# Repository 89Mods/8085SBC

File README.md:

# 8085 SBC

This repo contains all the source files for my i8085 SBC. For more information, see the READMEs in the sub-directories, and the writeup [on my website](https://tholin.dev/8085).

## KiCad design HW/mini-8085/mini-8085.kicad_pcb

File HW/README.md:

# Hardware

Here are the KiCad projects for all the hardware for the SBC, including the ROM carts.

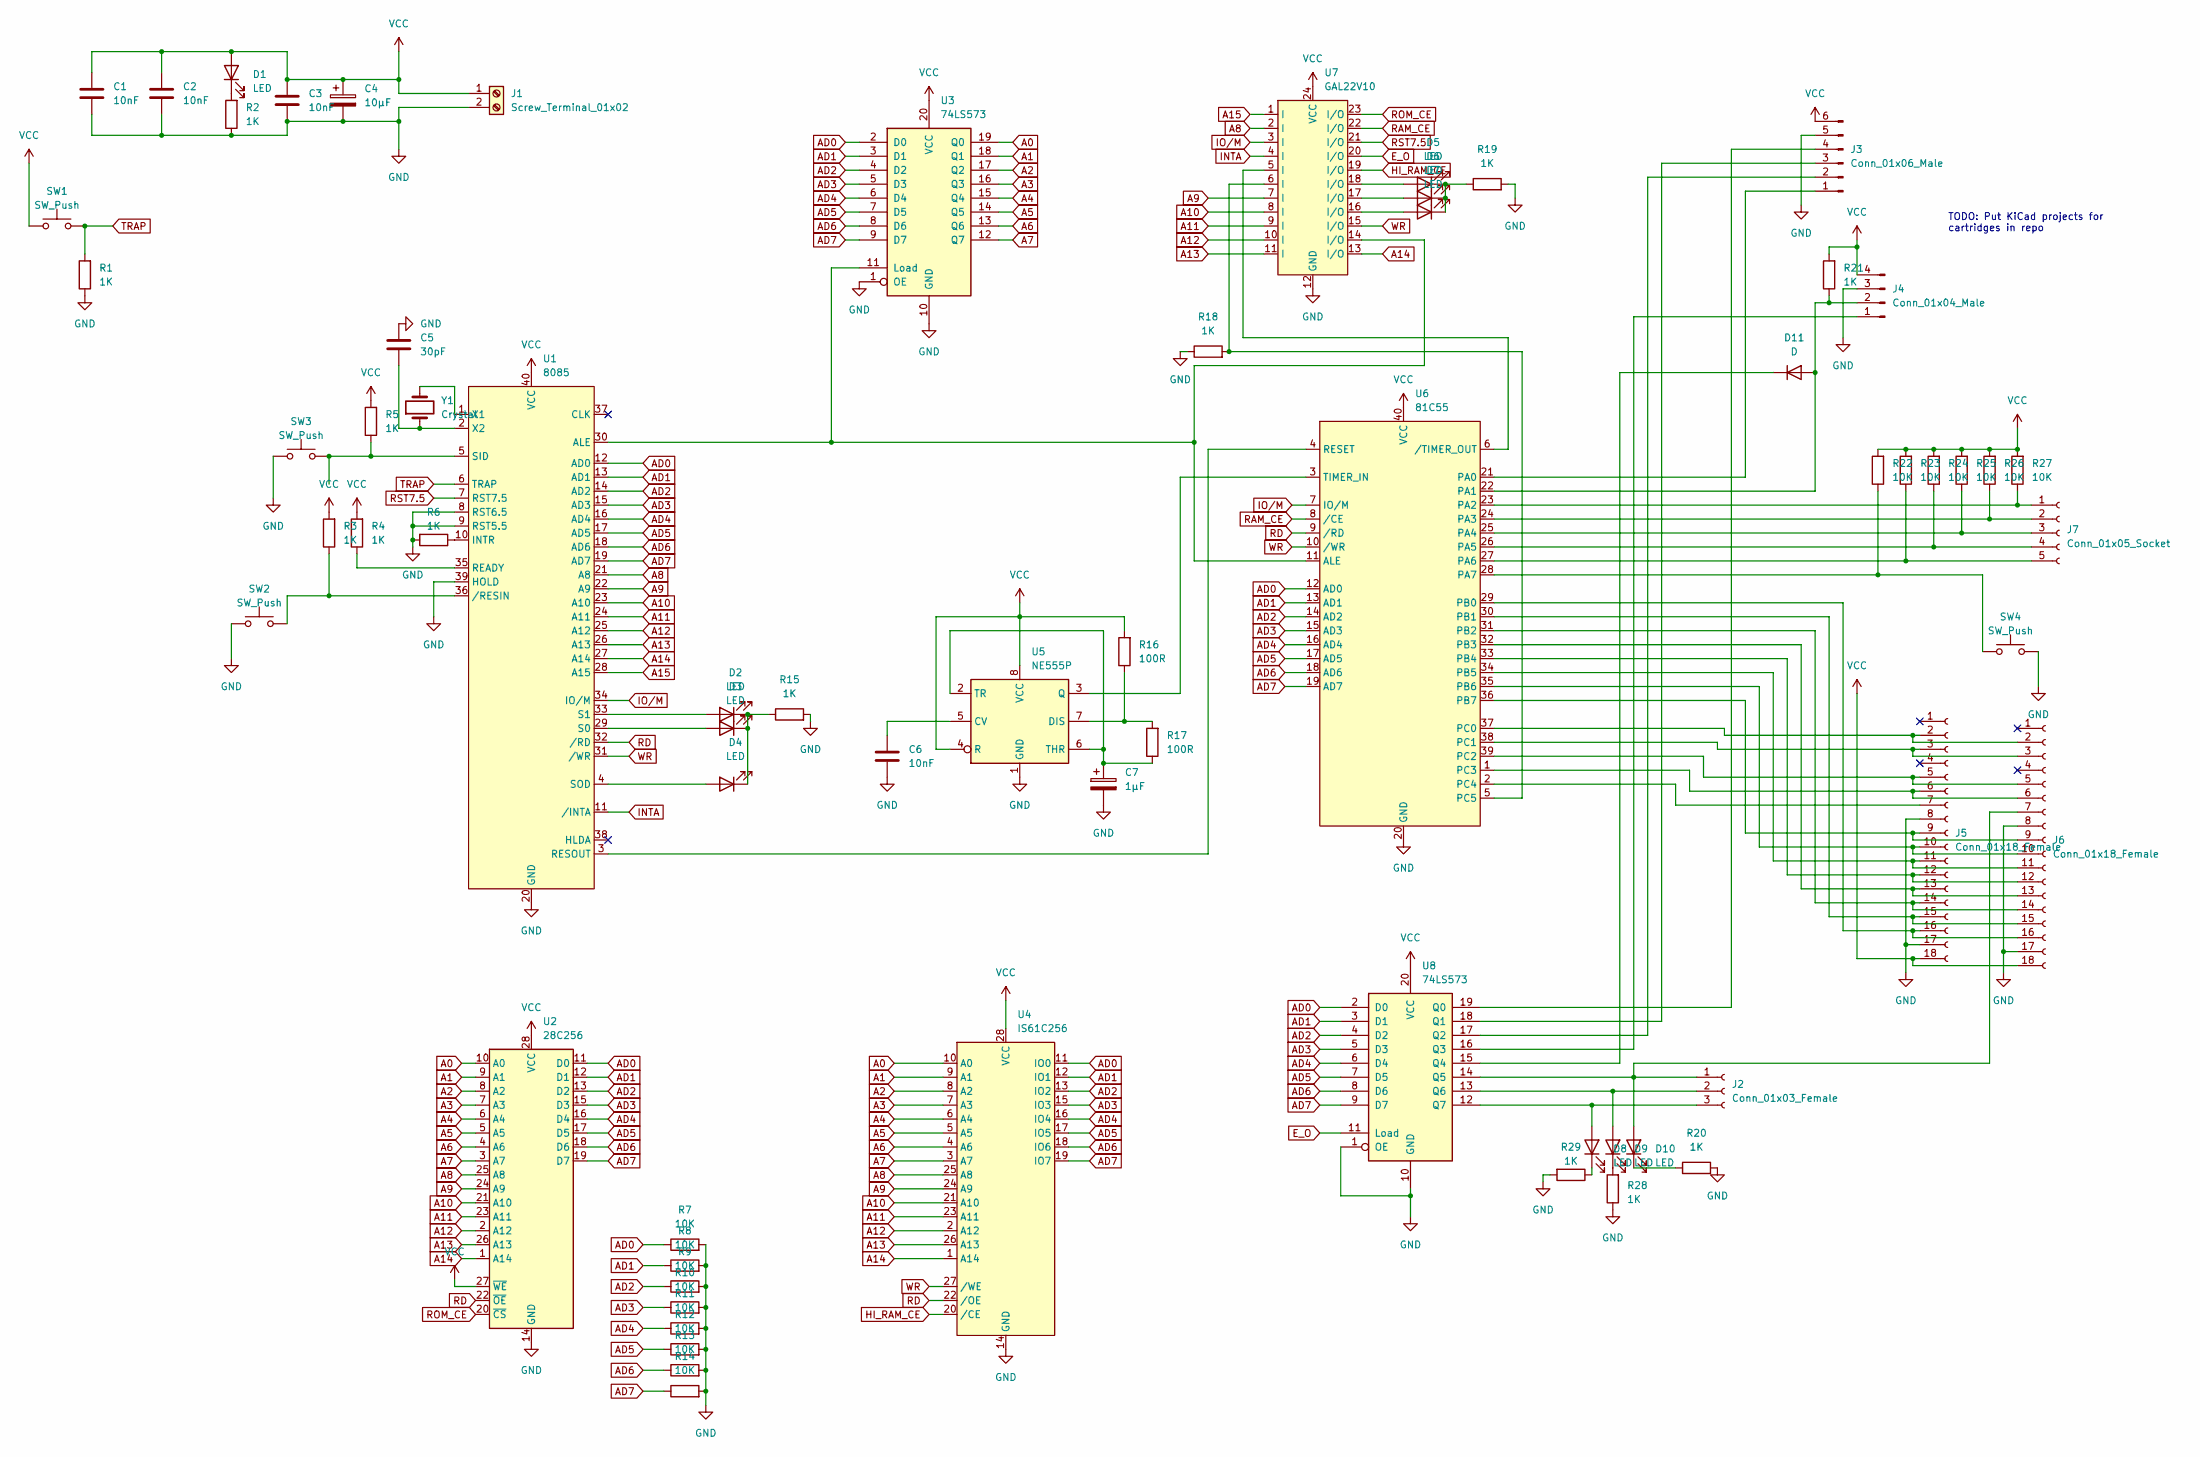
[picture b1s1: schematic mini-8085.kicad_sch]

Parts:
C1, C2, C3, C6: 10nF; C_Disc_D4.3mm_W1.9mm_P5.00mm
C4: 10µF; CP_Radial_D4.0mm_P1.50mm
C5: 30pF; C_Disc_D3.4mm_W2.1mm_P2.50mm
C7: 1µF; CP_Radial_D4.0mm_P1.50mm
D1, D2, D3, D4, D5, D6, D7, D8, D9, D10: LED; LED_D3.0mm
D11: D; D_A-405_P12.70mm_Horizontal
J1: Screw_Terminal_01x02; TerminalBlock_bornier-2_P5.08mm
J2: Conn_01x03_Female; PinHeader_1x03_P2.54mm_Vertical
J3: Conn_01x06_Male; PinHeader_1x06_P2.54mm_Vertical
J4: Conn_01x04_Male; PinHeader_1x04_P2.54mm_Vertical
J5, J6: Conn_01x18_Female; PinHeader_1x18_P2.54mm_Vertical
J7: Conn_01x05_Socket; PinHeader_1x05_P2.54mm_Vertical
R1, R2, R3, R4, R5, R6, R15, R18, R19, R20, R21, R28, R29: 1K; R_Axial_DIN0204_L3.6mm_D1.6mm_P7.62mm_Horizontal
R7, R8, R9, R10, R11, R12, R13, R14, R22, R23, R24, R25, R26, R27: 10K; R_Axial_DIN0204_L3.6mm_D1.6mm_P7.62mm_Horizontal
R16, R17: 100R; R_Axial_DIN0204_L3.6mm_D1.6mm_P7.62mm_Horizontal
SW1, SW2, SW3, SW4: SW_Push; SW_PUSH_6mm_H7.3mm
U1: 8085; DIP-40_W15.24mm
U2: 28C256; DIP-28_W15.24mm
U3, U8: 74LS573; DIP-20_W7.62mm
U4: IS61C256; DIP-28_W7.62mm
U5: NE555P; DIP-8_W7.62mm
U6: 81C55; DIP-40_W15.24mm
U7: GAL22V10; DIP-24_W7.62mm
Y1: Crystal; Resonator-2Pin_W7.0mm_H2.5mm

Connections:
A0: U2.10 (A0), U3.19 (Q0), U4.10 (A0)
A1: U2.9 (A1), U3.18 (Q1), U4.9 (A1)
A2: U2.8 (A2), U3.17 (Q2), U4.8 (A2)
A3: U2.7 (A3), U3.16 (Q3), U4.7 (A3)
A4: U2.6 (A4), U3.15 (Q4), U4.6 (A4)
A5: U2.5 (A5), U3.14 (Q5), U4.5 (A5)
A6: U2.4 (A6), U3.13 (Q6), U4.4 (A6)
A7: U2.3 (A7), U3.12 (Q7), U4.3 (A7)
A8: U1.21 (A8), U2.25 (A8), U4.25 (A8), U7.2 (I)
A9: U1.22 (A9), U2.24 (A9), U4.24 (A9), U7.7 (I)
A10: U1.23 (A10), U2.21 (A10), U4.21 (A10), U7.8 (I)
A11: U1.24 (A11), U2.23 (A11), U4.23 (A11), U7.9 (I)
A12: U1.25 (A12), U2.2 (A12), U4.2 (A12), U7.10 (I)
A13: U1.26 (A13), U2.26 (A13), U4.26 (A13), U7.11 (I)
A14: U1.27 (A14), U2.1 (A14), U4.1 (A14), U7.13 (I/O)
A15: U1.28 (A15), U7.1 (I)
AD0: R7.1, U1.12 (AD0), U2.11 (D0), U3.2 (D0), U4.11 (IO0), U6.12 (AD0), U8.2 (D0)
AD1: R8.1, U1.13 (AD1), U2.12 (D1), U3.3 (D1), U4.12 (IO1), U6.13 (AD1), U8.3 (D1)
AD2: R9.1, U1.14 (AD2), U2.13 (D2), U3.4 (D2), U4.13 (IO2), U6.14 (AD2), U8.4 (D2)
AD3: R10.1, U1.15 (AD3), U2.15 (D3), U3.5 (D3), U4.15 (IO3), U6.15 (AD3), U8.5 (D3)
AD4: R11.1, U1.16 (AD4), U2.16 (D4), U3.6 (D4), U4.16 (IO4), U6.16 (AD4), U8.6 (D4)
AD5: R12.1, U1.17 (AD5), U2.17 (D5), U3.7 (D5), U4.17 (IO5), U6.17 (AD5), U8.7 (D5)
AD6: R13.1, U1.18 (AD6), U2.18 (D6), U3.8 (D6), U4.18 (IO6), U6.18 (AD6), U8.8 (D6)
AD7: R14.1, U1.19 (AD7), U2.19 (D7), U3.9 (D7), U4.19 (IO7), U6.19 (AD7), U8.9 (D7)
E_O: U7.20 (I/O), U8.11 (Load)
GND: C1.2, C2.2, C3.2, C4.2, C5.1, C6.2, C7.2, J1.2, J3.5, J4.3, J5.8, J5.17, J6.8, J6.17, R1.1, R2.1, R6.2, R7.2, R8.2, R9.2, R10.2, R11.2, R12.2, R13.2, R14.2, R15.2, R18.1, R19.2, R20.2, R28.1, R29.2, SW2.1, SW3.1, SW4.2, U1.8 (RST6.5), U1.9 (RST5.5), U1.20 (GND), U1.39 (HOLD), U2.14 (GND), U3.1 (OE), U3.10 (GND), U4.14 (GND), U5.1 (GND), U6.20 (GND), U7.12 (GND), U8.1 (OE), U8.10 (GND)
HI_RAM_CE: U4.20 (/CE), U7.19 (I/O)
INTA: U1.11 (/INTA), U7.4 (I)
IO/M: U1.34 (IO/M), U6.7 (IO/M), U7.3 (I)
unnamed: D1.1 (K), R2.2
unnamed: D2.2 (A), U1.33 (S1)
unnamed: D2.1 (K), D3.1 (K), D4.1 (K), R15.1
unnamed: D3.2 (A), U1.29 (S0)
unnamed: D4.2 (A), U1.4 (SOD)
unnamed: D5.2 (A), U7.18 (I/O)
unnamed: D5.1 (K), D6.1 (K), D7.1 (K), R19.1
unnamed: D6.2 (A), U7.17 (I/O)
unnamed: D7.2 (A), U7.16 (I/O)
unnamed: D8.2 (A), J2.3, U8.12 (Q7)
unnamed: D8.1 (K), R29.1
unnamed: D9.2 (A), J2.2, U8.13 (Q6)
unnamed: D9.1 (K), R28.2
unnamed: D10.2 (A), J2.1, J6.7, U8.14 (Q5)
unnamed: D10.1 (K), R20.1
unnamed: D11.2 (A), J4.2, R21.1, U6.22 (PA1)
unnamed: D11.1 (K), U8.15 (Q4)
unnamed: J3.1, U6.21 (PA0)
unnamed: J3.2, U8.17 (Q2)
unnamed: J3.3, U8.18 (Q1)
unnamed: J3.4, U8.19 (Q0)
unnamed: J4.1, U8.16 (Q3)
unnamed: J5.2, J6.2, U6.37 (PC0)
unnamed: J5.3, J6.3, U6.38 (PC1)
unnamed: J5.5, J6.5, U6.39 (PC2)
unnamed: J5.6, J6.6, U6.1 (PC3)
unnamed: J5.7, U6.2 (PC4)
unnamed: J5.9, J6.9, U6.36 (PB7)
unnamed: J5.10, J6.10, U6.35 (PB6)
unnamed: J5.11, J6.11, U6.34 (PB5)
unnamed: J5.12, J6.12, U6.33 (PB4)
unnamed: J5.13, J6.13, U6.32 (PB3)
unnamed: J5.14, J6.14, U6.31 (PB2)
unnamed: J5.15, J6.15, U6.30 (PB1)
unnamed: J5.16, J6.16, U6.29 (PB0)
unnamed: J7.1, R27.1, U6.23 (PA2)
unnamed: J7.2, R26.1, U6.24 (PA3)
unnamed: J7.3, R25.1, U6.25 (PA4)
unnamed: J7.4, R24.1, U6.26 (PA5)
unnamed: J7.5, R23.1, U6.27 (PA6)
unnamed: U1.30 (ALE), U3.11 (Load), U6.11 (ALE), U7.14 (I/O)
unnamed: R6.1, U1.10 (INTR)
unnamed: R4.1, U1.35 (READY)
unnamed: U1.3 (RESOUT), U6.4 (RESET)
unnamed: R5.1, SW3.2, U1.5 (SID)
unnamed: U1.1 (X1), Y1.2
unnamed: C5.2, U1.2 (X2), Y1.1
unnamed: R3.1, SW2.2, U1.36 (/RESIN)
unnamed: C6.1, U5.5 (CV)
unnamed: R16.1, R17.2, U5.7 (DIS)
unnamed: U5.3 (Q), U6.3 (TIMER_IN)
unnamed: C7.1, R17.1, U5.2 (TR), U5.6 (THR)
unnamed: R22.1, SW4.1, U6.28 (PA7)
unnamed: R18.2, U6.5 (PC5), U7.6 (I)
unnamed: U6.6 (/TIMER_OUT), U7.5 (I)
RAM_CE: U6.8 (/CE), U7.22 (I/O)
RD: U1.32 (/RD), U2.22 (~OE), U4.22 (/OE), U6.9 (/RD)
ROM_CE: U2.20 (~CS), U7.23 (I/O)
RST7.5: U1.7 (RST7.5), U7.21 (I/O)
TRAP: R1.2, SW1.2, U1.6 (TRAP)
VCC: C1.1, C2.1, C3.1, C4.1, D1.2 (A), J1.1, J3.6, J4.4, J5.18, J6.18, R3.2, R4.2, R5.2, R16.2, R21.2, R22.2, R23.2, R24.2, R25.2, R26.2, R27.2, SW1.1, U1.40 (VCC), U2.27 (~WE), U2.28 (VCC), U3.20 (VCC), U4.28 (VCC), U5.4 (R), U5.8 (VCC), U6.40 (VCC), U7.24 (VCC), U8.20 (VCC)
WR: U1.31 (/WR), U4.27 (/WE), U6.10 (/WR), U7.15 (I/O)

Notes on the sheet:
TODO: Put KiCad projects for cartridges in repo

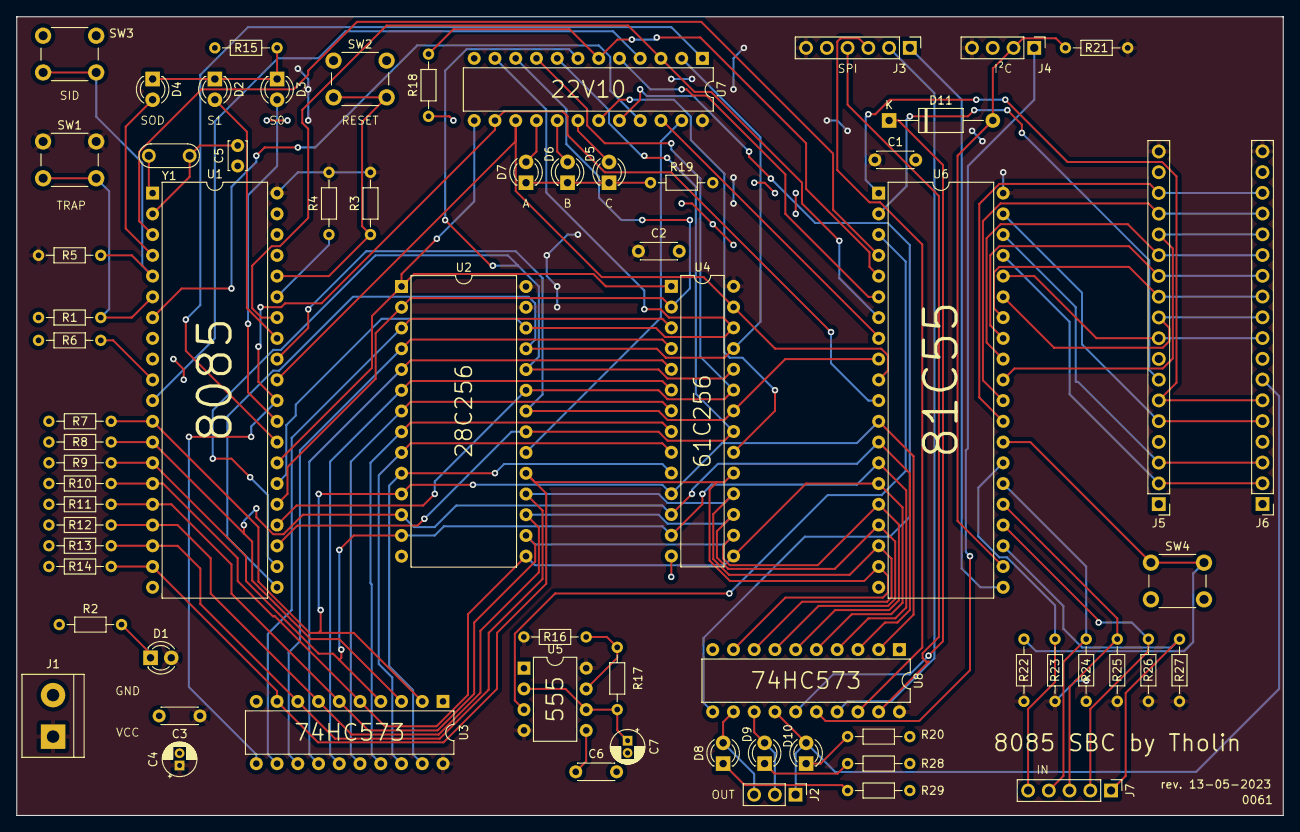
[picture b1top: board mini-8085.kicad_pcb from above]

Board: 2 copper layers, 155.1 x 97.8 mm, 67 parts (0 on the bottom side), 91 nets.

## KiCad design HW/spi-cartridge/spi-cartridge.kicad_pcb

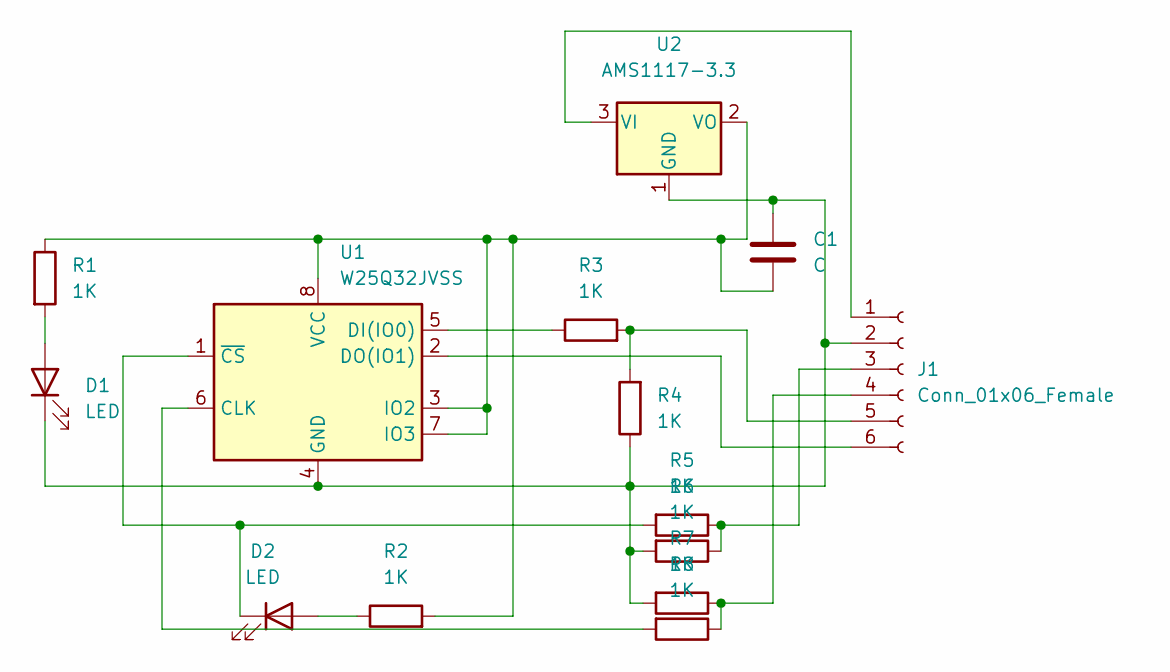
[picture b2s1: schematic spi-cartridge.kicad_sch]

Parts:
C1: C; C_1206_3216Metric
D1, D2: LED; LED_0402_1005Metric
J1: Conn_01x06_Female; PinHeader_1x06_P2.54mm_Vertical
R1, R2, R3, R4, R5, R6, R7, R8: 1K; R_0603_1608Metric
U1: W25Q32JVSS; SOIC-8_5.23x5.23mm_P1.27mm
U2: AMS1117-3.3; SOT-223-3_TabPin2

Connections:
unnamed: C1.1, D1.1 (K), J1.2, R4.1, R6.2, R7.2, U1.4 (GND), U2.1 (GND)
unnamed: D1.2 (A), R1.2
unnamed: D2.2 (A), R2.1
unnamed: J1.1, U2.3 (VI)
unnamed: J1.3, R5.1, R6.1
unnamed: J1.4, R7.1, R8.1
unnamed: J1.5, R3.2, R4.2
unnamed: J1.6, U1.2 (DO(IO1))
unnamed: C1.2, R1.1, R2.2, U1.3 (IO2), U1.7 (IO3), U1.8 (VCC), U2.2 (VO)
unnamed: D2.1 (K), R5.2, U1.1 (~CS)
unnamed: R3.1, U1.5 (DI(IO0))
unnamed: R8.2, U1.6 (CLK)

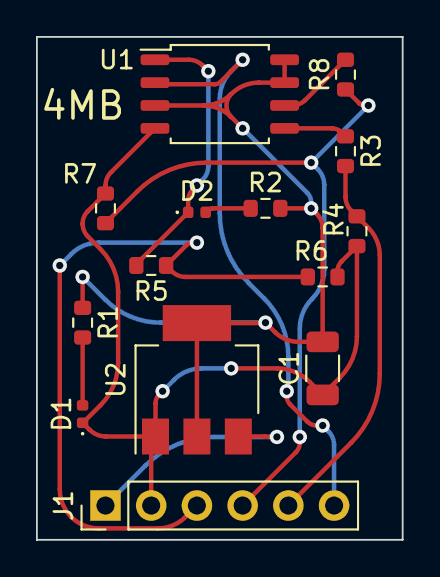
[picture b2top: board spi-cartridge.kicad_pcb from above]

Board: 2 copper layers, 20.3 x 27.9 mm, 14 parts (0 on the bottom side), 12 nets.

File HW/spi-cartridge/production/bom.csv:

Designator,Footprint,Quantity,Value,LCSC Part #
U2,SOT-223-3_TabPin2,1,AMS1117-3.3,
R8,R_0603_1608Metric,1,1K,
R7,R_0603_1608Metric,1,1K,
R6,R_0603_1608Metric,1,1K,
R5,R_0603_1608Metric,1,1K,
R4,R_0603_1608Metric,1,1K,
R3,R_0603_1608Metric,1,1K,
R2,R_0603_1608Metric,1,1K,
D2,LED_0402_1005Metric,1,LED,
C1,C_1206_3216Metric,1,C,
J1,PinHeader_1x06_P2.54mm_Vertical,1,Conn_01x06_Female,
D1,LED_0402_1005Metric,1,LED,
R1,R_0603_1608Metric,1,1K,
U1,SOIC-8_5.23x5.23mm_P1.27mm,1,W25Q32JVSS,

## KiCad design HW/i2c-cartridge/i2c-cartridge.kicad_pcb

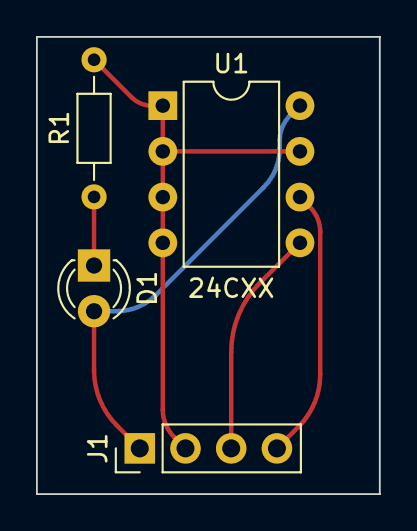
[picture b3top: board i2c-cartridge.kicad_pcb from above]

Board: 2 copper layers, 19.1 x 25.4 mm, 4 parts (0 on the bottom side), 5 nets.

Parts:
D1: LED; LED_D3.0mm
J1: Conn_01x04_Female; PinHeader_1x04_P2.54mm_Vertical
R1: 1K; R_Axial_DIN0204_L3.6mm_D1.6mm_P7.62mm_Horizontal
U1: 24Cxx; DIP-8_W7.62mm

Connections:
unnamed: D1.1 (K), R1.1
unnamed: D1.2 (A), J1.1, U1.8 (VCC)
unnamed: J1.2, R1.2, U1.1 (A0), U1.2 (A1), U1.3 (A2), U1.4 (GND), U1.7 (WP)
unnamed: J1.3, U1.5 (SDA)
unnamed: J1.4, U1.6 (SCL)

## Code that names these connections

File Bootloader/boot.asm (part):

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
; PORTB is UART data
; 573 bit 5 is UART CS
; PC3 is WE
; PC2 is RE
; PC1 is C/D
; PC0 is RES

; PORTA desc:
; 0: SPI DI (device’s DO)
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
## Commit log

2023-08-01 Initial commit.
2023-08-27 Test program for timer interrupt.
2024-01-17 Experiment with 8085 undocumented instructions.
